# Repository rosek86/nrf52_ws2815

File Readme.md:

# nRF52840 WS2815 driver

There is only MacOS bootstrap / compilation support. Linux can be easily acheived by updating links in the bootstrap.sh file.

## Bootstrap

Script downloads nRF SDK and gcc compiler.

```bash
./bootstrap.sh
```

## Build

```bash
mkdir Debug && cd Debug
cmake -GNinja -DCMAKE_TOOLCHAIN_FILE=../cmake/toolchain.cmake -DCMAKE_BUILD_TYPE=Debug ..
ninja
```

## Flash with nrfjprog

```bash
ninja flash_jlink
```

## Flash via JLinkExe

```bash
cd Debug # or Release
JLinkExe -Device NRF52 -Speed 4000 -If SWD -Autoconnect 1
r
exec SetRTTAddr 0x0000000020001a08
loadfile src/nrf52_ws2815.hex
g
```

## View RTT logs

Connect via JLinkExe first, then using other terminal:

```bash
JLinkRTTClient
```

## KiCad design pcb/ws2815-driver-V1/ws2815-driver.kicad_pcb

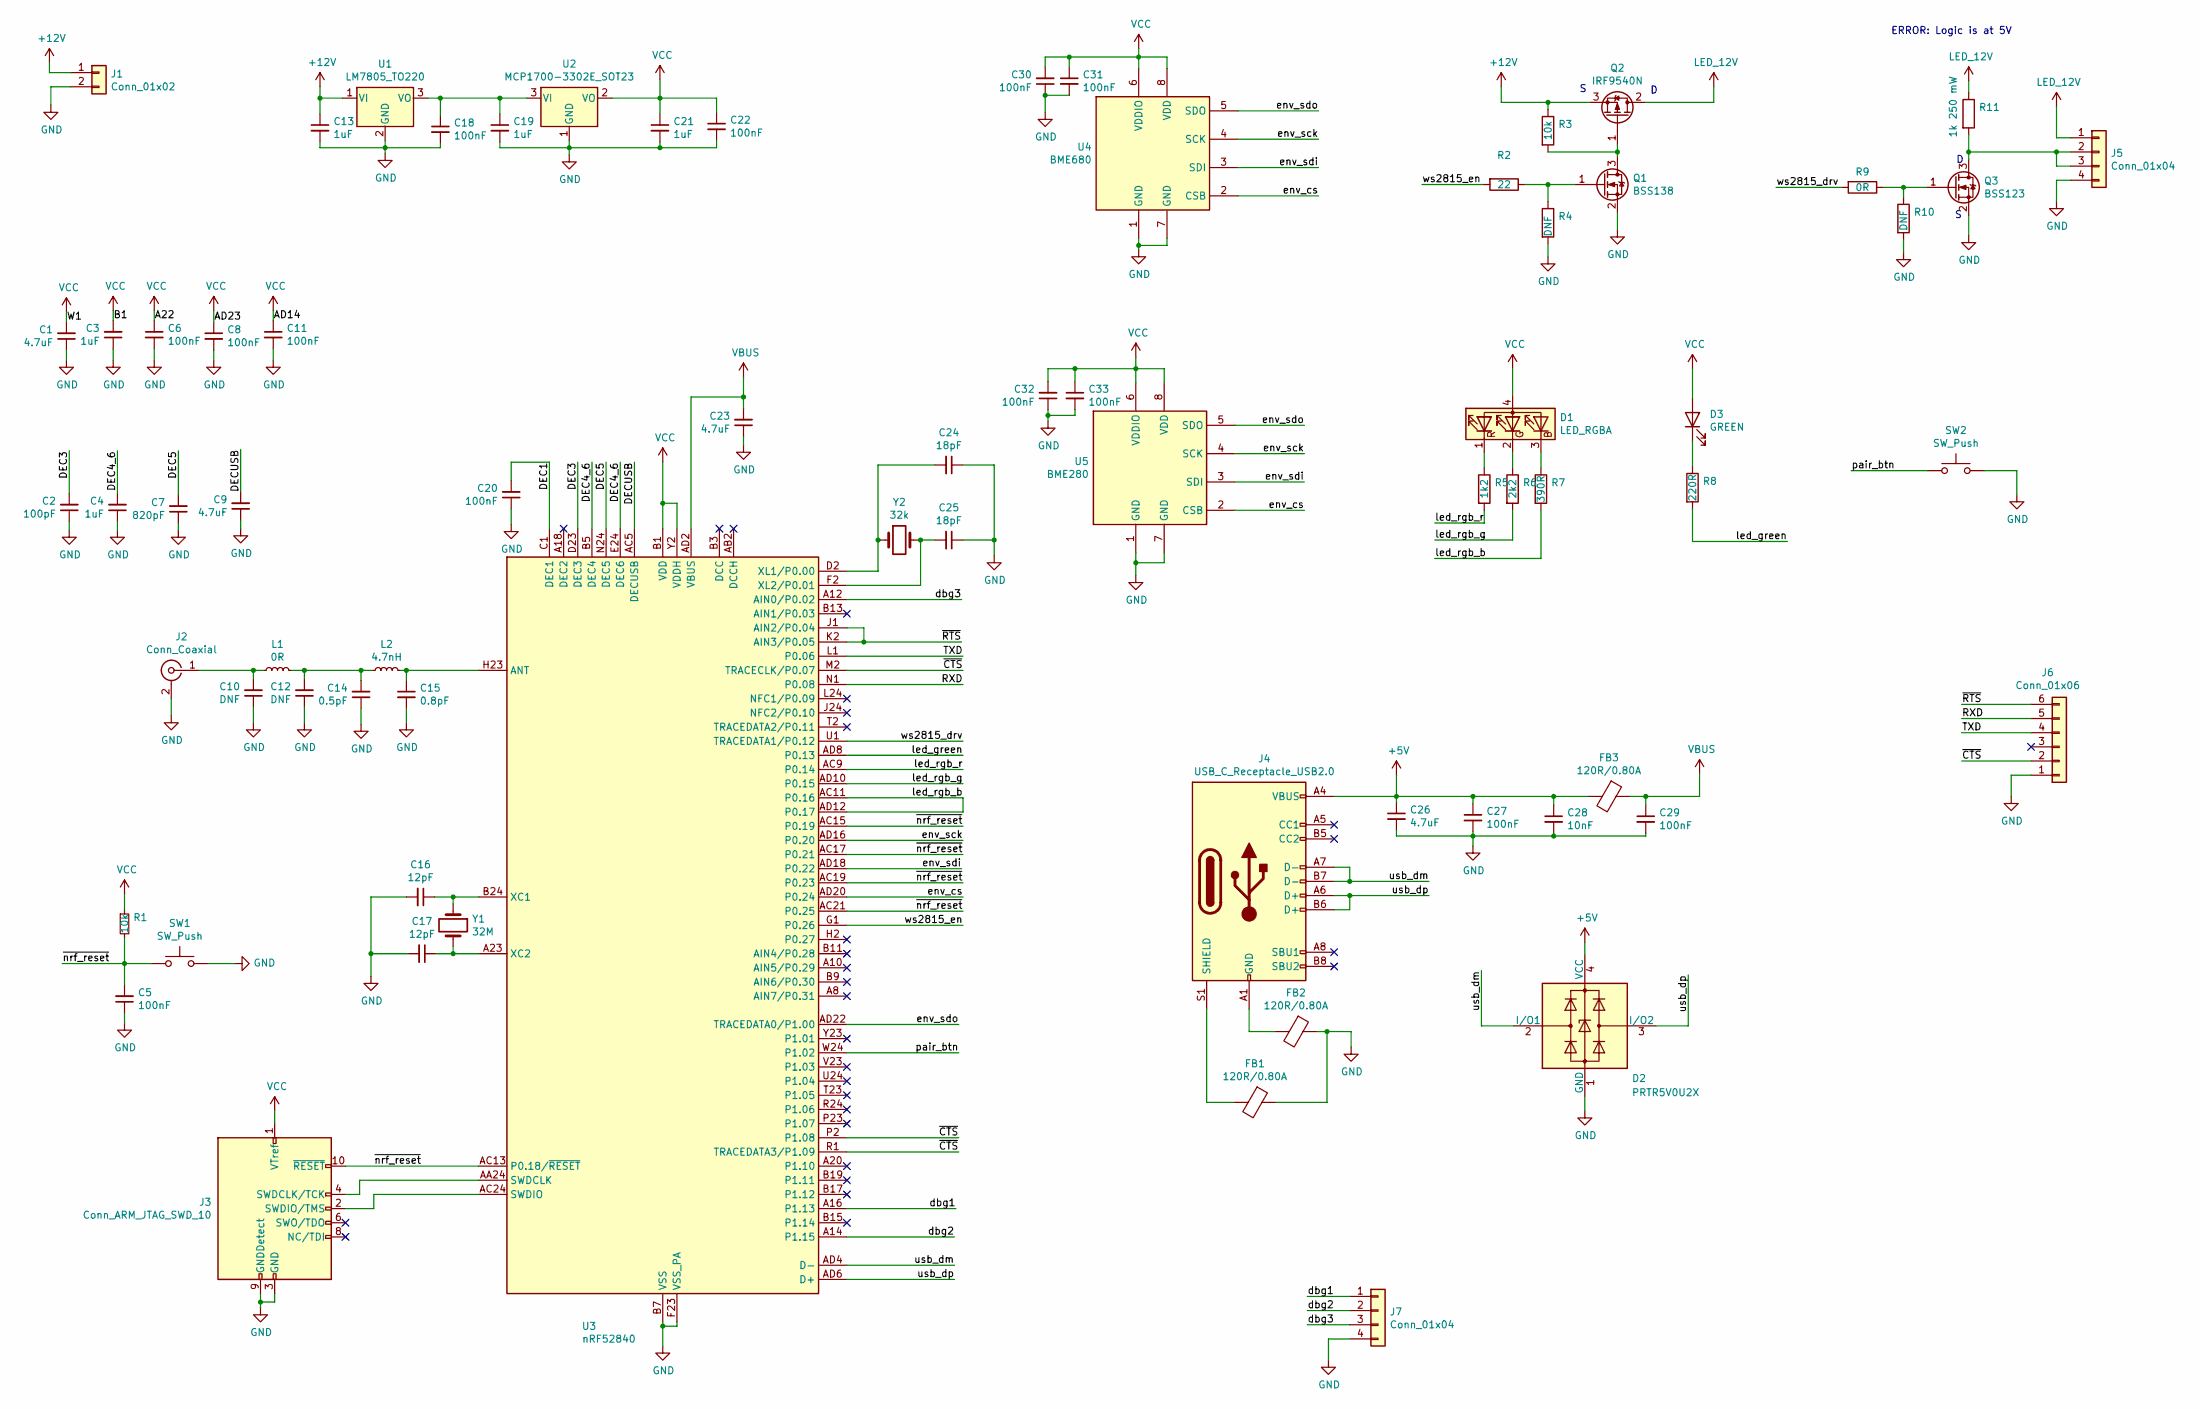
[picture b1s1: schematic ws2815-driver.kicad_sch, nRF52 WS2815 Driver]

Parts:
C1, C9, C23, C26: 4.7uF; C_0805_2012Metric_Pad1.15x1.40mm_HandSolder
C2: 100pF; C_0603_1608Metric_Pad1.05x0.95mm_HandSolder
C3, C4, C13, C19, C21: 1uF; C_0603_1608Metric_Pad1.05x0.95mm_HandSolder
C5, C6, C8, C11, C18, C20, C22, C27, C29: 100nF; C_0603_1608Metric_Pad1.05x0.95mm_HandSolder
C7: 820pF; C_0603_1608Metric_Pad1.05x0.95mm_HandSolder
C10, C12: DNF; C_0402_1005Metric
C14: 0.5pF; C_0402_1005Metric
C15: 0.8pF; C_0402_1005Metric
C16, C17: 12pF; C_0603_1608Metric_Pad1.05x0.95mm_HandSolder
C24, C25: 18pF; C_0603_1608Metric_Pad1.05x0.95mm_HandSolder
C28: 10nF; C_0603_1608Metric_Pad1.05x0.95mm_HandSolder
C30, C31, C32, C33: 100nF; C_0402_1005Metric
D1: LED_RGBA; brightek_1.6x1.5_rgb_led; Part Number 2SA0603VGB01JT07
D2: PRTR5V0U2X; SOT-143
D3: GREEN; LED_0603_1608Metric_Pad1.05x0.95mm_HandSolder
FB1, FB2, FB3: 120R/0.80A; L_0805_2012Metric_Pad1.15x1.40mm_HandSolder; Part Number BK2125HS121-T
J1: Conn_01x02; PhoenixContact_MSTBA_2,5_2-G-5,08_1x02_P5.08mm_Horizontal; Part Number DB2EK-5.08-2P, DB2ER-5.08-2P
J2: Conn_Coaxial; SMA_Molex_73251-1153_EdgeMount_Horizontal
J3: Conn_ARM_JTAG_SWD_10; PinHeader_2x05_P1.27mm_Vertical
J4: USB_C_Receptacle_USB2.0; USB_C_Receptacle_Palconn_UTC16-G
J5: Conn_01x04; PhoenixContact_MSTBA_2,5_4-G-5,08_1x04_P5.08mm_Horizontal; Part Number DB2EK-5.08-4P, DB2ER-5.08-4P
J6: Conn_01x06; PinHeader_1x06_P2.54mm_Vertical
J7: Conn_01x04; PinHeader_1x04_P2.54mm_Vertical; Part Number DB2EK-5.08-4P, DB2ER-5.08-4P
L1: 0R; L_0402_1005Metric
L2: 4.7nH; L_0402_1005Metric
Q1: BSS138; SOT-23
Q2: IRF9540N; TO-220-3_Horizontal_TabDown
Q3: BSS123; SOT-23
R1, R3: 10k; R_0603_1608Metric_Pad1.05x0.95mm_HandSolder
R2: 22; R_0603_1608Metric_Pad1.05x0.95mm_HandSolder
R4, R10: DNF; R_0603_1608Metric_Pad1.05x0.95mm_HandSolder
R5: 1k2; R_0603_1608Metric_Pad1.05x0.95mm_HandSolder
R6: 2k2; R_0603_1608Metric_Pad1.05x0.95mm_HandSolder
R7: 390R; R_0603_1608Metric_Pad1.05x0.95mm_HandSolder
R8: 220R; R_0603_1608Metric_Pad1.05x0.95mm_HandSolder
R9: 0R; R_0603_1608Metric_Pad1.05x0.95mm_HandSolder
R11: 1k 250 mW; R_1206_3216Metric_Pad1.42x1.75mm_HandSolder
SW1, SW2: SW_Push; SW_SPST_TL3342
U1: LM7805_TO220; TO-220-3_Horizontal_TabDown
U2: MCP1700-3302E_SOT23; SOT-23
U3: nRF52840; Nordic_AQFN-73-1EP_7x7mm_P0.5mm
U4: BME680; Bosch_LGA-8_3x3mm_P0.8mm_ClockwisePinNumbering
U5: BME280; Bosch_LGA-8_2.5x2.5mm_P0.65mm_ClockwisePinNumbering
Y1: 32M; Crystal_SMD_2016-4Pin_2.0x1.6mm; Part Number Q22FA12800393
Y2: 32k; Crystal_SMD_2012-2Pin_2.0x1.2mm_HandSoldering; Part Number SC-20S,32.768kHz,20PPM,12.5pF

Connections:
+5V: C26.1, C27.1, C28.1, D2.4 (VCC), FB3.2, J4.A4 (VBUS), J4.A9 (VBUS), J4.B4 (VBUS), J4.B9 (VBUS)
+12V: C13.1, J1.1, Q2.3 (S), R3.1, U1.1 (VI)
+LED_12V: J5.1, Q2.2 (D), R11.1
/DEC1: C20.2, U3.C1 (DEC1)
/DEC3: C2.2, U3.D23 (DEC3)
/DEC4_6: C4.2, U3.B5 (DEC4), U3.E24 (DEC6)
/DEC5: C7.2, U3.N24 (DEC5)
/DECUSB: C9.2, U3.AC5 (DECUSB)
/RXD: J6.5, U3.N1 (P0.08)
/TXD: J6.4, U3.L1 (P0.06)
/dbg1: J7.1, U3.A16 (P1.13)
/dbg2: J7.2, U3.A14 (P1.15)
/dbg3: J7.3, U3.A12 (AIN0/P0.02)
/env_cs: U3.AD20 (P0.24), U4.2 (CSB), U5.2 (CSB)
/env_sck: U3.AD16 (P0.20), U4.4 (SCK), U5.4 (SCK)
/env_sdi: U3.AD18 (P0.22), U4.3 (SDI), U5.3 (SDI)
/env_sdo: U3.AD22 (TRACEDATA0/P1.00), U4.5 (SDO), U5.5 (SDO)
/led_green: R8.2, U3.AD8 (P0.13)
/led_rgb_b: R7.2, U3.AC11 (P0.16), U3.AD12 (P0.17)
/led_rgb_g: R6.2, U3.AD10 (P0.15)
/led_rgb_r: R5.2, U3.AC9 (P0.14)
/pair_btn: SW2.1, U3.W24 (P1.02)
/usb_dm: D2.2 (I/O1), J4.A7 (D-), J4.B7 (D-), U3.AD4 (D-)
/usb_dp: D2.3 (I/O2), J4.A6 (D+), J4.B6 (D+), U3.AD6 (D+)
/ws2815_drv: R9.2, U3.U1 (TRACEDATA1/P0.12)
/ws2815_en: R2.2, U3.G1 (P0.26)
/~CTS: J6.2, U3.M2 (TRACECLK/P0.07), U3.P2 (P1.08), U3.R1 (TRACEDATA3/P1.09)
/~RTS: J6.6, U3.J1 (AIN2/P0.04), U3.K2 (AIN3/P0.05)
/~nrf_reset: C5.2, J3.10 (~RESET), R1.2, SW1.1, U3.AC13 (P0.18/~RESET), U3.AC15 (P0.19), U3.AC17 (P0.21), U3.AC19 (P0.23), U3.AC21 (P0.25)
GND: C1.1, C2.1, C3.1, C4.1, C5.1, C6.2, C7.1, C8.2, C9.1, C10.1, C11.2, C12.1, C13.2, C14.1, C15.2, C16.2, C17.2, C18.2, C19.2, C20.1, C21.2, C22.2, C23.1, C24.1, C25.1, C26.2, C27.2, C28.2, C29.2, C30.1, C31.2, C32.1, C33.2, D2.1 (GND), FB1.1, FB2.1, J1.2, J2.2 (Ext), J3.3 (GND), J3.5 (GND), J3.9 (GNDDetect), J5.4, J6.1, J7.4, Q1.2 (S), Q3.2 (S), R4.2, R10.2, SW1.2, SW2.2, U1.2 (GND), U2.1 (GND), U3.B7 (VSS), U3.EP (VSS), U3.F23 (VSS_PA), U4.1 (GND), U4.7 (GND), U5.1 (GND), U5.7 (GND)
unnamed: C10.2, J2.1 (In), L1.1
unnamed: C12.2, C14.2, L1.2, L2.1
unnamed: C15.1, L2.2, U3.H23 (ANT)
unnamed: C16.1, U3.B24 (XC1), Y1.1
unnamed: C17.1, U3.A23 (XC2), Y1.3
unnamed: C18.1, C19.1, U1.3 (VO), U2.3 (VI)
unnamed: C24.2, U3.D2 (XL1/P0.00), Y2.1
unnamed: C25.2, U3.F2 (XL2/P0.01), Y2.2
unnamed: D1.1 (RK), R5.1
unnamed: D1.2 (GK), R6.1
unnamed: D1.3 (BK), R7.1
unnamed: D3.1 (K), R8.1
unnamed: FB1.2, J4.S1 (SHIELD)
unnamed: FB2.2, J4.A1 (GND), J4.A12 (GND), J4.B1 (GND), J4.B12 (GND)
unnamed: J3.2 (SWDIO/TMS), U3.AC24 (SWDIO)
unnamed: J3.4 (SWDCLK/TCK), U3.AA24 (SWDCLK)
unnamed: J5.2, J5.3, Q3.3 (D), R11.2
unnamed: Q1.1 (G), R2.1, R4.1
unnamed: Q1.3 (D), Q2.1 (G), R3.2
unnamed: Q3.1 (G), R9.1, R10.1
VBUS: C23.2, C29.1, FB3.1, U3.AD2 (VBUS)
VCC: C1.2, C3.2, C6.1, C8.1, C11.1, C21.1, C22.1, C30.2, C31.1, C32.2, C33.1, D1.4 (A), D3.2 (A), J3.1 (VTref), R1.1, U2.2 (VO), U3.A22 (VDD), U3.AD14 (VDD), U3.AD23 (VDD), U3.B1 (VDD), U3.W1 (VDD), U3.Y2 (VDDH), U4.6 (VDDIO), U4.8 (VDD), U5.6 (VDDIO), U5.8 (VDD)

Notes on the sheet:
ERROR: Logic is at 5V

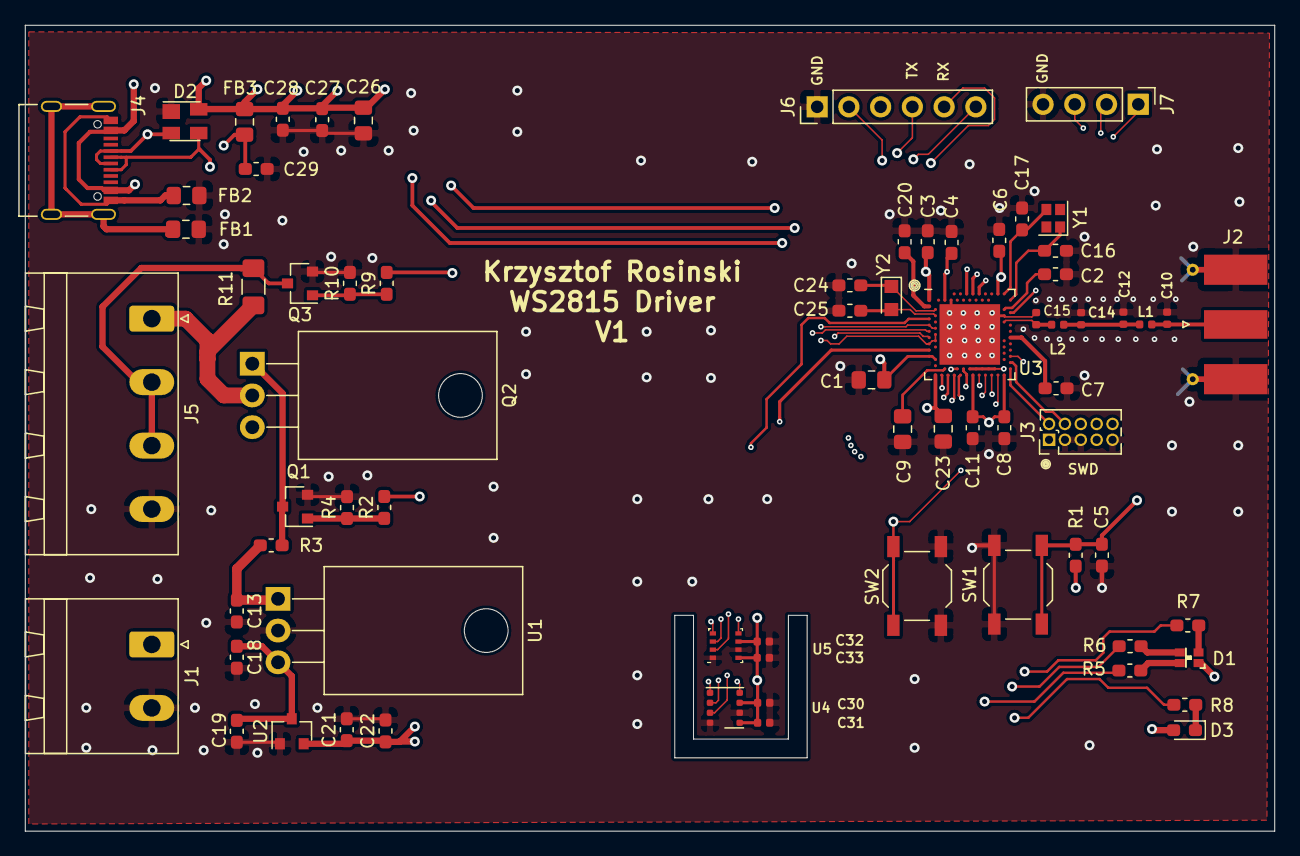
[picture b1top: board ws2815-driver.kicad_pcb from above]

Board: 4 copper layers, 100.0 x 64.5 mm, 71 parts (0 on the bottom side), 52 nets.

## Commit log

2019-11-03 drive 300 leds strip
2019-11-03 drive 300 leds strip, improvements
2019-11-03 update clock calculation comment
2019-11-06 cleanup, enable rtt logs, updated readme
2019-11-06 cleanup
2019-11-06 double buffering
2019-11-07 separate low level ws2815 driver from main
2019-11-09 non blocking loop, ws2815 driver rewrite
2019-11-09 program tested against slow mo
2019-11-11 handle inverted drivers, bugfix, add rgb to hsv conversion
2019-12-08 add custom board
2019-12-10 initial effects implementation
2019-12-11 ws2815 to/from rgb bugfix
2019-12-14 blink and breath effects, fixes
2019-12-14 rainbow cycle, flame effects
2019-12-15 change effect on button press
2019-12-15 initial gamma correction
2019-12-27 minor effects improvements
2022-01-02 Add pcb design
